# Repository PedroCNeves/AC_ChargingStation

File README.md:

⚠️ WARNING — READ BEFORE USE

This Arduino Uno code and Shield are provided as a starter project for educational purposes only. They are intended to help you learn about EV charging concepts and are sufficient to demonstrate basic charging station functionality. This project is not compliant with safety standards or certifications required for production use.

ELECTRICAL HAZARD: Working with AC mains power is dangerous and can result in serious injury, death, electric shock, fire, or property damage. If you are not experienced with high-voltage electrical systems, consult a licensed electrician before attempting to build or test this project.

By using this code and hardware, you accept full responsibility for your safety and any consequences that may arise.

This is a repository for a learning and development project (not a finished product).
This repository contains:
- Code for Arduino Uno to work as an EV AC Charging Station.
- KiCAD Schematic and PCB of a Shield for Arduino Uno to make the hardware for an EV AC Charging Station.
- Gerber files to fabricate the Shield.
- BOM to assemble the Shield.

Instructions to execute this learning project: https://www.udemy.com/course/electric-vehicle-charging-from-theory-to-practice/?referralCode=AC67637479A66E6618A2

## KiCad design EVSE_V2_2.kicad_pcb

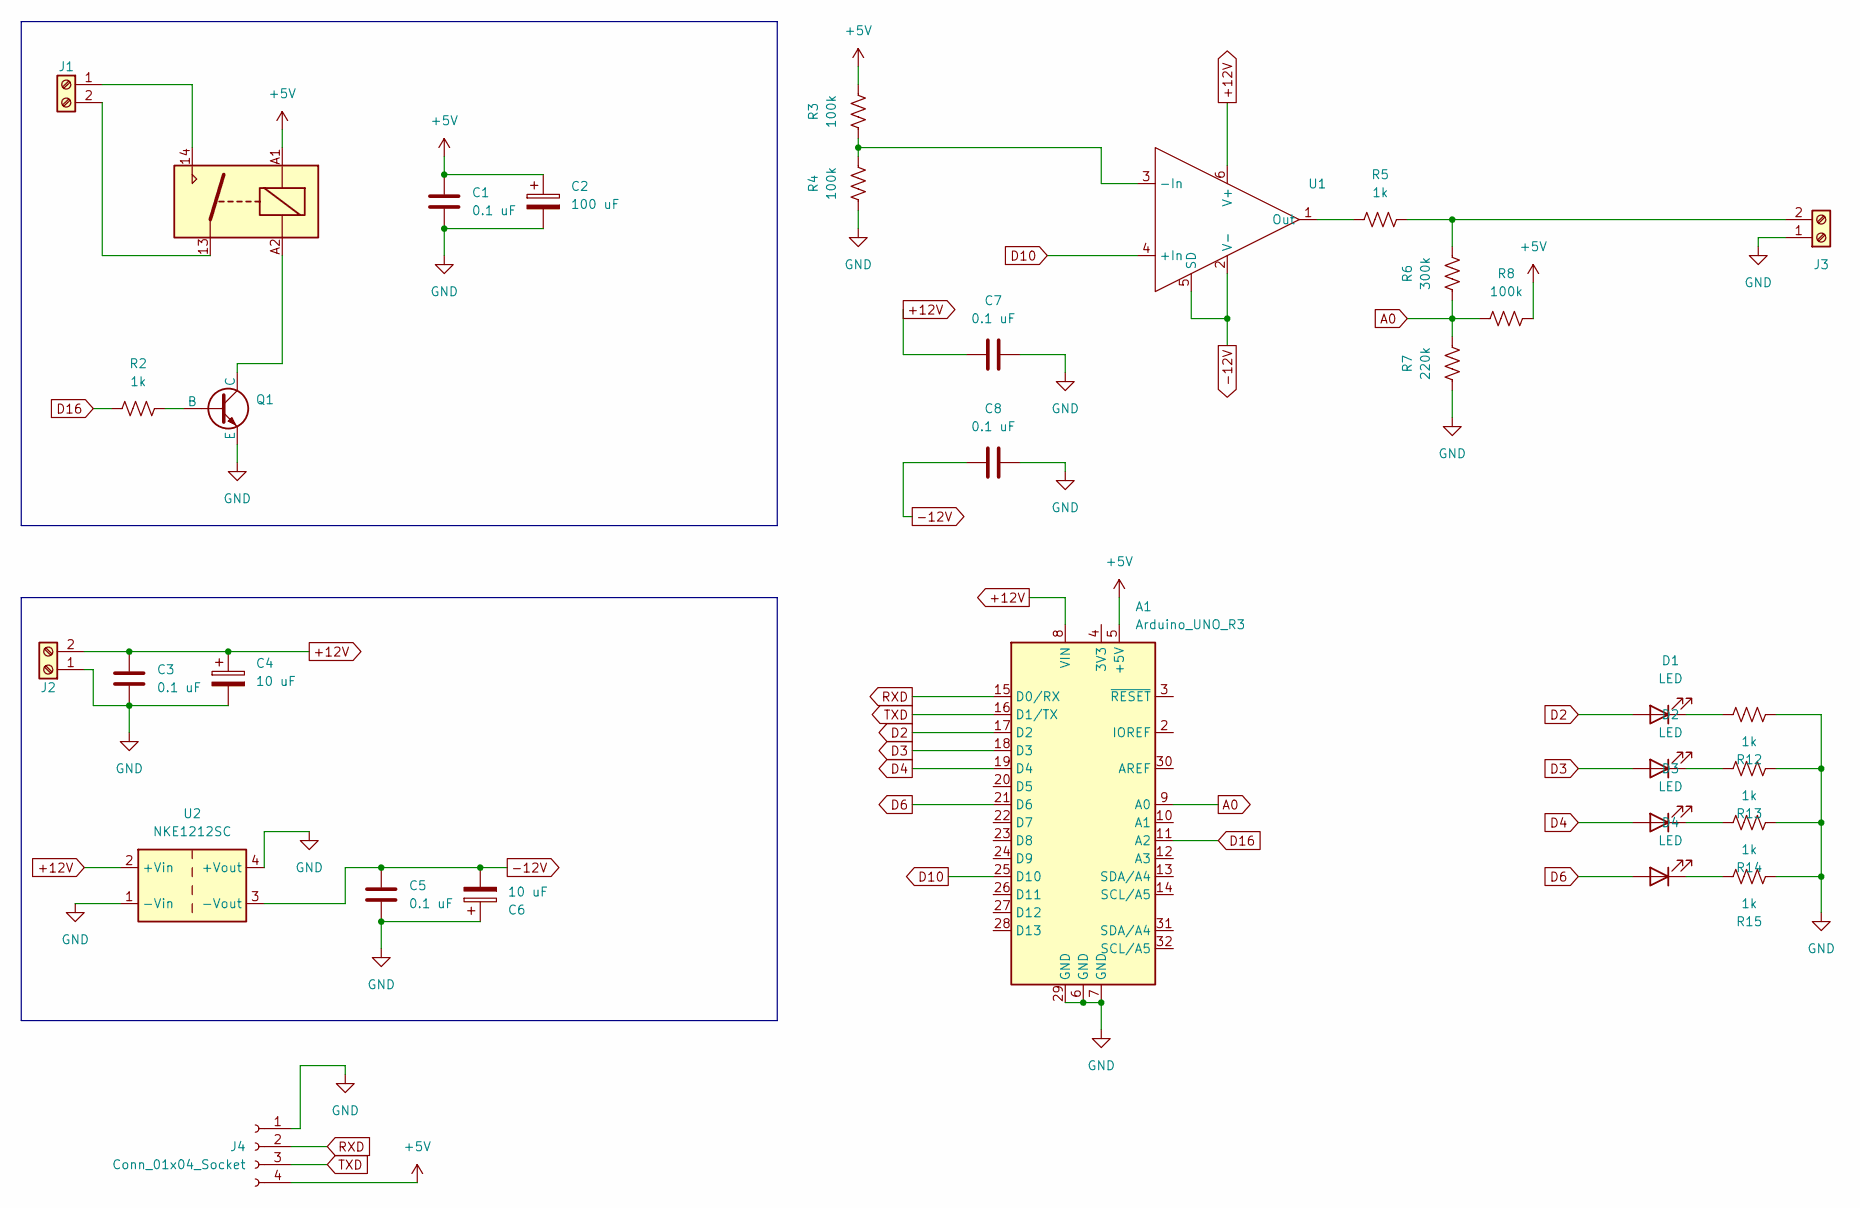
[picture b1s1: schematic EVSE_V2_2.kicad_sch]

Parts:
A1: Arduino_UNO_R3
C1, C3, C5, C7, C8: 0.1 uF; C_1206_3216Metric
C2: 100 uF; CP_Radial_D6.3mm_P2.50mm
C4, C6: 10 uF; CP_Radial_D4.0mm_P1.50mm
D1, D2, D3, D4: LED; LED_1206_3216Metric
J1, J2, J3: Screw_Terminal_01x02; Lever 2 - 2,5 2-5,0
J4: Conn_01x04_Socket; FanPinHeader_1x04_P2.54mm_Vertical
K1: Relay_SPST-NO; Relay_TE_SPST_16A
Q1: NPN; TO-92_3
R2, R5, R12, R13, R14, R15: 1k; R_1206_3216Metric
R3, R4, R8: 100k; R_1206_3216Metric
R6: 300k; R_1206_3216Metric
R7: 220k; R_1206_3216Metric
U1: SOT-23-6
U2: NKE1212SC

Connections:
+5V: A1.5 (+5V), C1.1, C2.1, J4.4, K1.A1, R3.2, R8.2
+12V: A1.8 (VIN), C3.1, C4.1, C7.1, J2.2, U1.6 (V+), U2.2 (+Vin)
-12V: C5.1, C6.2, C8.1, U1.2 (V-), U1.5 (SD), U2.3 (-Vout)
A0: A1.9 (A0), R6.1, R7.2, R8.1
D2: A1.17 (D2), D1.2 (A)
D3: A1.18 (D3), D2.2 (A)
D4: A1.19 (D4), D3.2 (A)
D6: A1.21 (D6), D4.2 (A)
D10: A1.25 (D10), U1.4 (+In)
D16: A1.11 (A2), R2.1
GND: A1.6 (GND), A1.7 (GND), A1.29 (GND), C1.2, C2.2, C3.2, C4.2, C5.2, C6.1, C7.2, C8.2, J2.1, J3.1, J4.1, Q1.3 (E), R4.1, R7.1, R12.1, R13.1, R14.1, R15.1, U2.1 (-Vin), U2.4 (+Vout)
unnamed: D1.1 (K), R12.2
unnamed: D2.1 (K), R13.2
unnamed: D3.1 (K), R14.2
unnamed: D4.1 (K), R15.2
unnamed: J1.1, K1.14
unnamed: J1.2, K1.13
unnamed: J3.2, R5.2, R6.2
unnamed: Q1.2 (B), R2.2
unnamed: K1.A2, Q1.1 (C)
unnamed: R3.1, R4.2, U1.3 (-In)
unnamed: R5.1, U1.1 (Out)
RXD: A1.15 (D0/RX), J4.2
TXD: A1.16 (D1/TX), J4.3

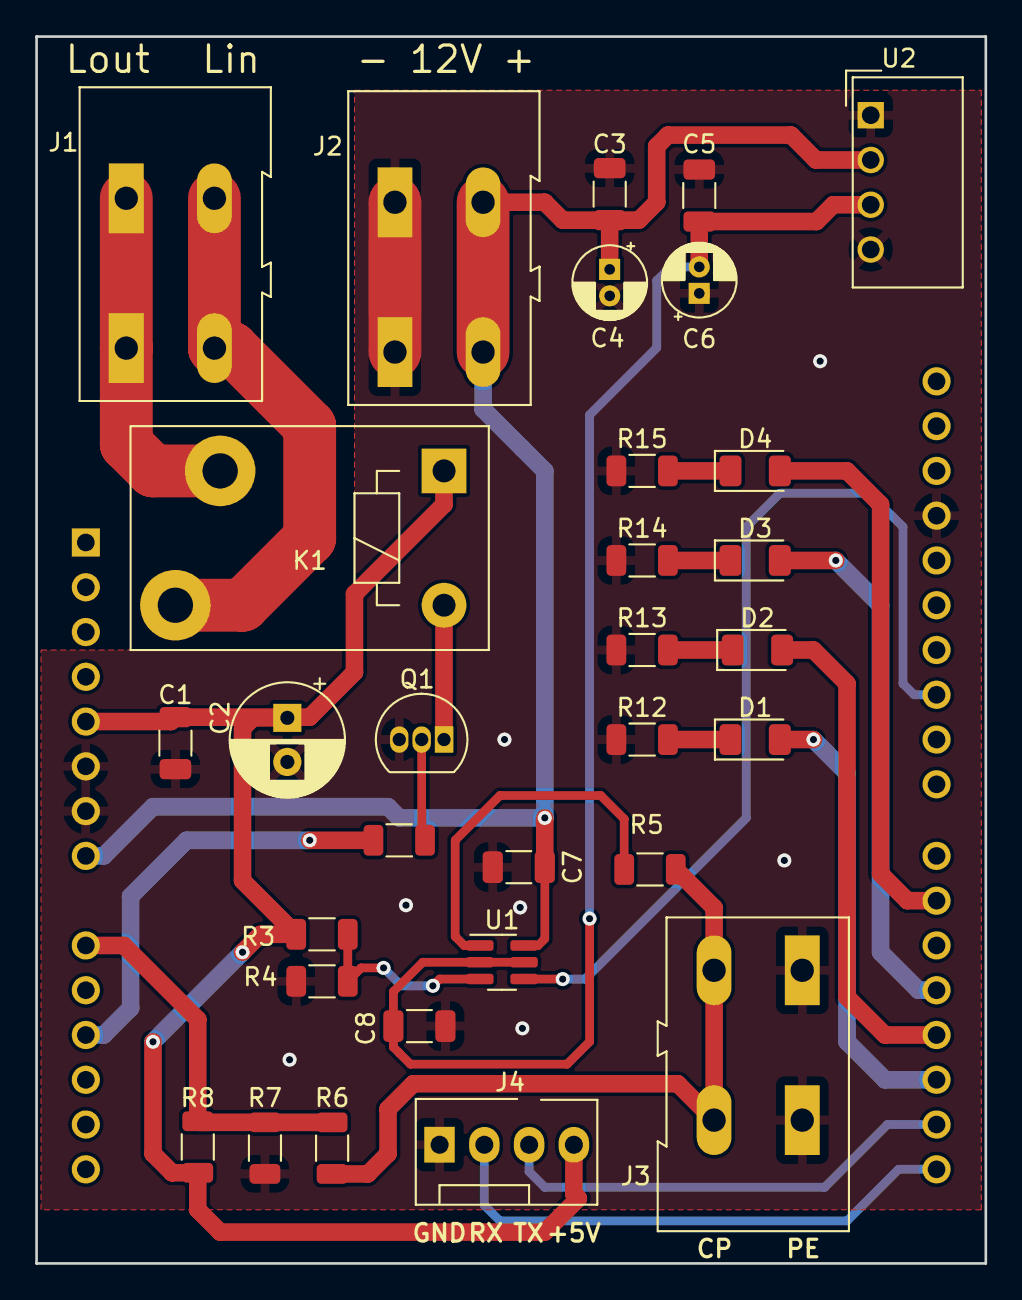
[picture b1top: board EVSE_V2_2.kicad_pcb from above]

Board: 2 copper layers, 53.8 x 69.6 mm, 32 parts (1 on the bottom side), 24 nets.

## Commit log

2024-04-18 Added v1 of all resource files
2024-05-03 Create LICENSE
    Add a CERN OHL licence. Read more on https://cern-ohl.web.cern.ch/
    CERN has developed the CERN Open Hardware Licence (CERN OHL) as a legal tool to promote collaboration among hardware designers and support the freedom to use, study, modify, share and distribute hard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
2024-11-04 This Commit contains the code more organized and the second version of the Arduino Uno shield. This version outsources the power connection to an external contactor.
2024-11-04 Edit Readme
